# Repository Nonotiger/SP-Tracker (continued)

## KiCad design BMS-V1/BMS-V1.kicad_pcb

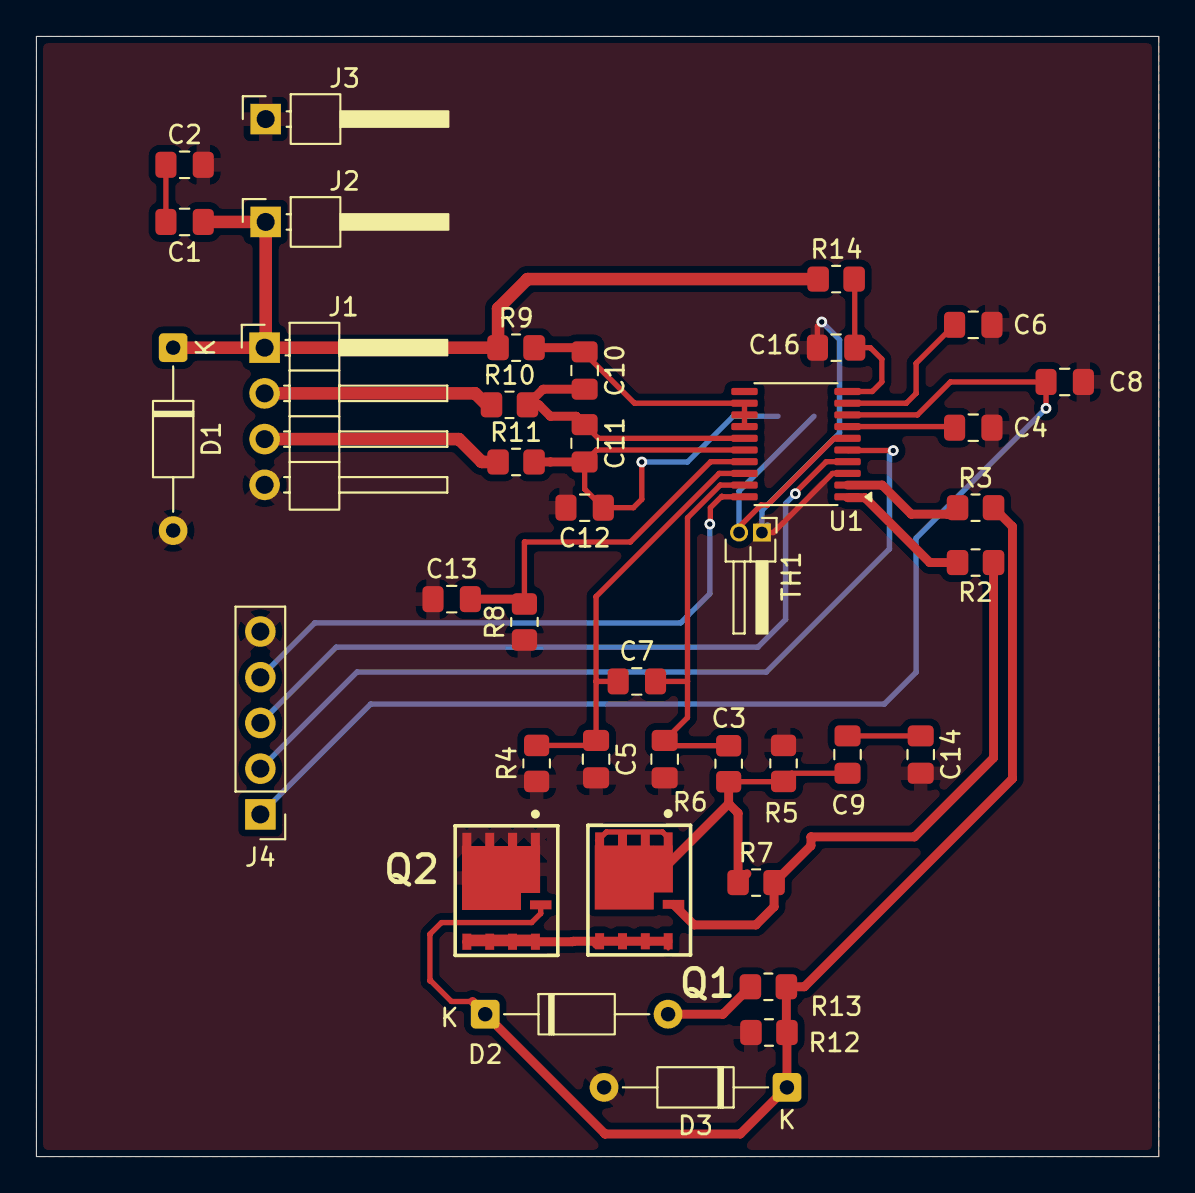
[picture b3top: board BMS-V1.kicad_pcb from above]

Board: 2 copper layers, 62.4 x 62.2 mm, 40 parts (1 on the bottom side), 27 nets.

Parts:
C1, C2, C3, C5, C7, C9, C14: 0.1u; C_0805_2012Metric_Pad1.18x1.45mm_HandSolder
C4, C6, C10, C11, C12, C13, C16: 1uF; C_0805_2012Metric_Pad1.18x1.45mm_HandSolder
C8: 4.7uF; C_0805_2012Metric_Pad1.18x1.45mm_HandSolder
D1: 26V; D_DO-35_SOD27_P10.16mm_Horizontal
D2: 100V; D_DO-35_SOD27_P10.16mm_Horizontal
D3: 16V; D_DO-35_SOD27_P10.16mm_Horizontal
J1: Conn_01x04_Pin; PinHeader_1x04_P2.54mm_Horizontal
J2: BATT+; PinHeader_1x01_P2.54mm_Horizontal
J3: BATT-; PinHeader_1x01_P2.54mm_Horizontal
J4: Conn_01x05_Pin; PinHeader_1x05_P2.54mm_Vertical
Q1, Q2: IQDH35N03LM5CG; IFX-PG-TTFN-9-2-V
R1: 10k; R_0805_2012Metric_Pad1.20x1.40mm_HandSolder
R2, R3, R14: 1k; R_0805_2012Metric_Pad1.20x1.40mm_HandSolder
R4, R6: 100; R_0805_2012Metric_Pad1.20x1.40mm_HandSolder
R5, R12: 1M; R_0805_2012Metric_Pad1.20x1.40mm_HandSolder
R7: 10M; R_0805_2012Metric_Pad1.20x1.40mm_HandSolder
R8, R9, R10, R11: 75; R_0805_2012Metric_Pad1.20x1.40mm_HandSolder
R13: 3.3M; R_0805_2012Metric_Pad1.20x1.40mm_HandSolder
TH1: 103AT; PinHeader_1x02_P1.27mm_Horizontal
U1: BQ76920PW; TSSOP-20_4.4x6.5mm_P0.65mm

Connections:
CHG: D2.1 (K), D3.1 (K), Q2.9 (GATE_9), R3.2, R12.1, R13.2
Cell1: J1.3, R11.1
Cell2: J1.2, R10.1
Cell3: C1.1, D1.1 (K), J1.1, J2.1 (Pin_1_1), R9.1, R14.1
DSG: Q1.9 (GATE_9), R2.1, R7.2
GND: C2.2, C3.2, C4.1, C5.2, C6.1, C8.1, C12.2, C13.1, C14.2, C16.2, D1.2 (A), D3.2 (A), J1.4, J3.1 (Pin_1_1), J4.5, Q2.1, R4.1, R5.1, R8.1, R13.1, TH1.1, U1.3 (VSS)
unnamed: C1.2, C2.1
unnamed: C9.2, C14.1
unnamed: D2.2 (A), R12.2
unnamed: C8.2, J4.1, U1.8 (REGOUT)
unnamed: J4.2, U1.5 (SCL)
unnamed: J4.3, U1.4 (SDA)
unnamed: J4.4, U1.20 (ALERT)
unnamed: Q1.2 (DRAIN2_6), Q2.2 (DRAIN2_6)
unnamed: C9.1, Q1.1 (SOURCE1_1), R5.2, R6.1, R7.1
unnamed: C16.1, R14.2, U1.10 (BAT)
unnamed: C4.2, U1.7 (CAP1)
unnamed: R3.1, U1.2 (CHG)
unnamed: R2.2, U1.1 (DSG)
unnamed: C6.2, U1.9 (REGSRC)
unnamed: R1.2, TH1.2, U1.6 (TS1)
unnamed: C13.2, R8.2, U1.17 (VC0)
unnamed: C11.2, C12.1, R1.1, R11.2, U1.16 (VC1)
unnamed: C10.2, C11.1, R10.2, U1.15 (VC2)
unnamed: C10.1, R9.2, U1.12 (VC5), U1.13 (VC4), U1.14 (VC3)
SRN: C3.1, C7.2, R6.2, U1.19 (SRN)
SRP: C5.1, C7.1, R4.2, U1.18 (SRP)
